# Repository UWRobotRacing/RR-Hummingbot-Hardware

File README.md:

# RobotRacing2019-Hardware
This repo contains hardware includes mech &amp; electrical. Firmware code will also locate here.

## Code Style
1. Use `space: 2` for tabs
2. Preferrably to put all private global variables within a local struct called `FileName_data_S`, and declare a static global variable `FileName_data_S fileName_data;` & initialized with a `memset(&fileName_data, 0, sizeof(fileName_data));` 
    - Reason: to keep global vars more organized and trackable
3. use **cameralCase** preferrably for the variable names and function names
4. For libraries, we shall append a unique space name in CAP before each public functions such as `uint8_t RF24_read(void)`
5. All private data & functions should be declared with a `static`, so it clearly indicate the function/data is private.

## Key Notes
1. For Mac users to use uart for debugging, you will be required to install [FT232R driver](https://www.ftdichip.com/Drivers/VCP.htm), please see instructions here: - [MacOS High Sierra 10.13.3 FTDI Driver Fix](https://superuser.com/questions/1135730/how-to-release-reset-serial-port-ftdi-devices-mac-osx)
2. NXP mcuxpresso API for our chip: [link](https://mcuxpresso.nxp.com/api_doc/dev/1008/group__lpspi__driver.html#ae03069cfdcf680ee5fd81e077b81bc18), and you might be required to login, please register an account if necessary.
    - you can also download the API, which contains chip specific examples \[SDK_2.5.0_MKE14F512xxx16\]
3. Our M4 chip: MKE14F512xxx16
  
## Hardware Resources
### Reedy Sonic 540 Sensor 6Pins

IMHO the connector is "EFRA standard" (RC cars)
see here page 25
[http://mgm-compro.com/manuals/en-man...-071011-a1.pdf](http://mgm-compro.com/manuals/en-manual-x-series-071011-a1.pdf)
 - Pin #1 – black wire, ground potential (minus)
 - Pin #2 – orange wire, sensor phase C
 - Pin #3 – white wire, sensor phase B
 - Pin #4 – green wire, sensor phase A
 - Pin #5 – blue wire, motor temperature sensing, 10 k NTC
 - (other end of sensor is on ground potential, pin #1)
 - Pin #6 – red wire, sensors feeding, +5.0 V ± 10%.
(supply voltage for sensors provide controller, don´t connect external voltage !)

#### interfacing hall sensors:
https://tutorial.cytron.io/2018/07/04/measuring-dc-motor-rpm-through-built-in-hall-sensor-encoder/
https://www.nxp.com/docs/en/application-note/AN2892.pdf

### Steering_Encoder:
https://www.digikey.ca/product-detail/en/cui-inc/AMT203-V/102-2050-ND/2278846

### ESC Arduino
https://www.instructables.com/id/ESC-Programming-on-Arduino-Hobbyking-ESC/ 
1000us - 2000us

If a 0-180° servo is designed to respond to 1000-2000 µs pulses, it interprets 1000 µs as “0°” and 2000 µs as “180°.” But, with default pulse width limits range of 544-2400 µs, the Arduino will send a signal of ~1000 µs for an angle of 44°. Sweeping from 1000 to 2000 µs would then only translate to a ~90° swing of the servo arm instead of a full 180°. This, and other potential issues can be avoided if microseconds are used instead of angles in degrees, or if the optional pulse width floor and ceiling parameters are defined in pin setup for each servo.
```c
#define Servo_VERSION           2     // software version of this library
#define MIN_PULSE_WIDTH       544     // the shortest pulse sent to a servo  
#define MAX_PULSE_WIDTH      2400     // the longest pulse sent to a servo 
#define DEFAULT_PULSE_WIDTH  1500     // default pulse width when servo is attached
#define REFRESH_INTERVAL    20000     // minumim time to refresh servos in microseconds 

```

### nRF24L01
1. [Intro](https://components101.com/wireless/nrf24l01-pinout-features-datasheet)
2. [DataSheet](https://components101.com/sites/default/files/component_datasheet/nRF24L01%20Datasheet.pdf)
3. [Enhancing](https://www.instructables.com/id/Enhanced-NRF24L01/)
4. [Detailed Explaination](http://www.diyembedded.com/tutorials/nrf24l01_0/nrf24l01_tutorial_0.pdf)
5. [Colorful InDepth Descriptions](https://lastminuteengineers.com/nrf24l01-arduino-wireless-communication/)

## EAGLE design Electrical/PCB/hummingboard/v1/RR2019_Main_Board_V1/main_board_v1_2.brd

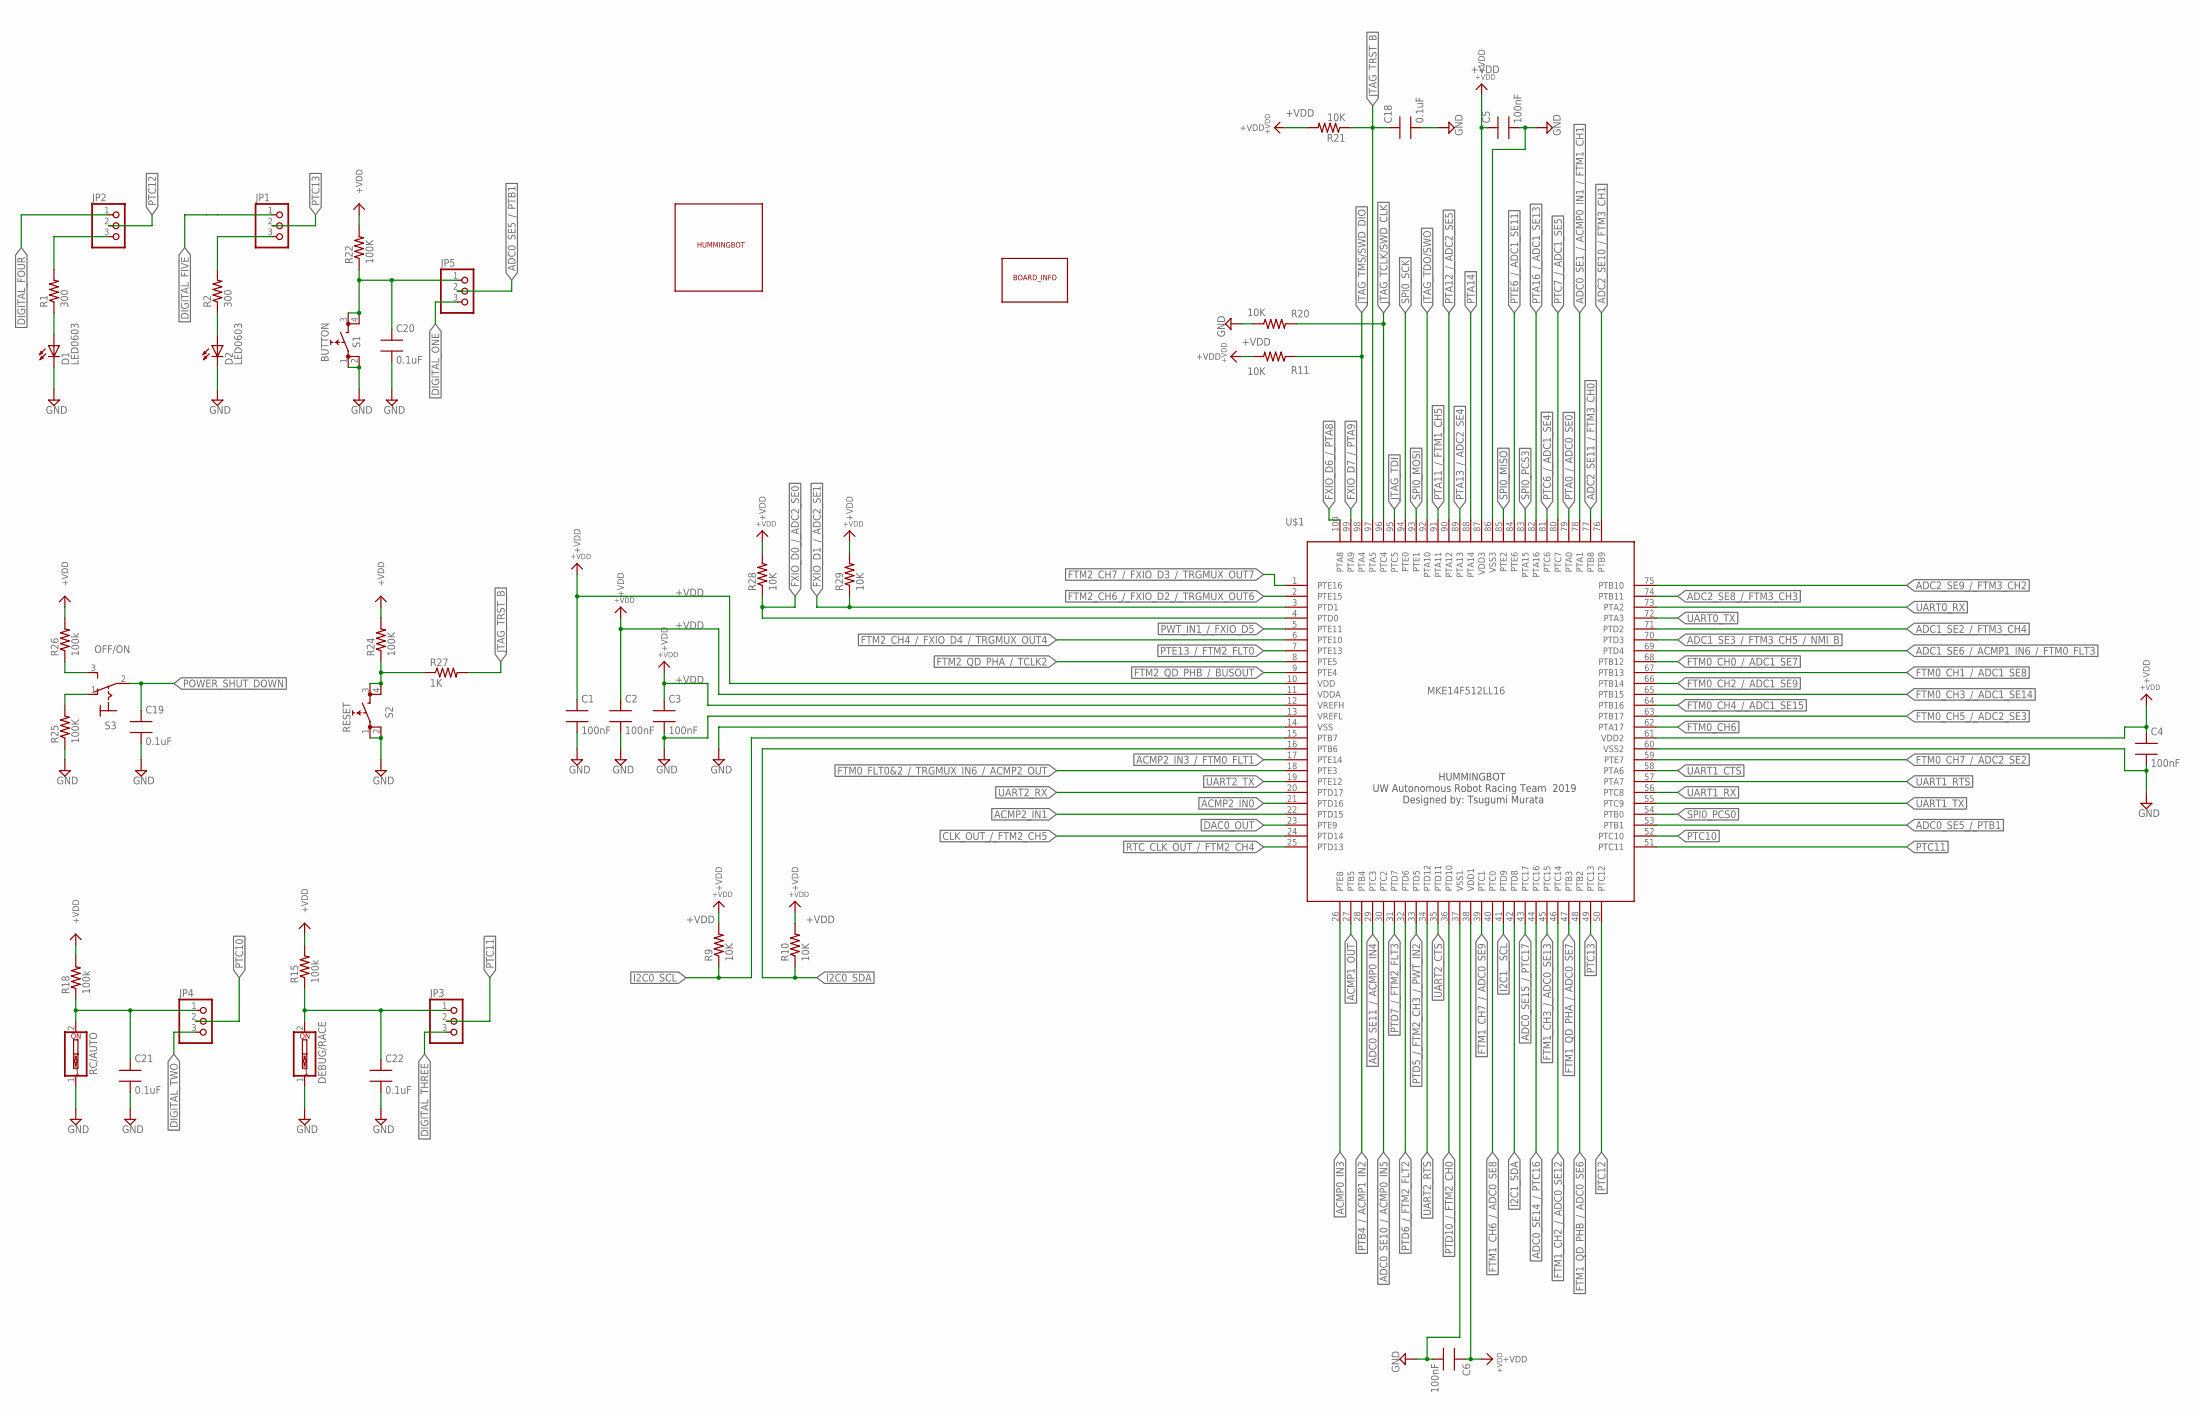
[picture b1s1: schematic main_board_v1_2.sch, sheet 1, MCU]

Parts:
C1, C2, C3, C4, C5, C6: 100nF; 0603SMT
C18, C19, C20, C21, C22: 0.1uF; 0603SMT
D1, D2: LED0603; 0603SMT
DEBUG/RACE: SW_DIP-1; EDG-01
JP1, JP2, JP3, JP4, JP5: PINHD-1X3; 1X03
R1, R2: 300; 0603SMT
R9, R10, R11, R20, R21, R28, R29: 10K; 0603SMT
R15, R18, R26: 100k; 0603SMT
R22, R24, R25: 100K; 0603SMT
R27: 1K; 0603SMT
RC/AUTO: SW_DIP-1; EDG-01
S1: BUTTON; TACT_SWITCH_SMT
S2: RESET; TACT_SWITCH_SMT
S3: OFF/ON; M9040P
U$1: MKE14F512LL16; LQFP100
U$38: BOARD_INFO
U$44: TEAM_LOGO

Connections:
+VDD: C1.1, C2.1, C3.1, C4.1, C5.1, C6.1, R9.2, R10.2, R11.2, R15.2, R18.2, R21.2, R22.2, R24.2, R26.2, R28.2, R29.2, U$1.10 (VDD), U$1.11 (VDDA), U$1.12 (VREFH), U$1.38 (VDD1), U$1.61 (VDD2), U$1.87 (VDD3); also elsewhere on the board
ACMP0_IN3: U$1.26 (PTE8); also elsewhere on the board
ACMP1_OUT: U$1.27 (PTB5); also elsewhere on the board
ACMP2_IN0: U$1.21 (PTD16); also elsewhere on the board
ACMP2_IN1: U$1.22 (PTD15); also elsewhere on the board
ACMP2_IN3_/_FTM0_FLT1: U$1.17 (PTE14); also elsewhere on the board
ADC0_SE1_/_ACMP0_IN1_/_FTM1_CH1: U$1.78 (PTA1); also elsewhere on the board
ADC0_SE5_/_PTB1: JP5.2, U$1.53 (PTB1)
ADC0_SE10_/_ACMP0_IN5: U$1.30 (PTC2); also elsewhere on the board
ADC0_SE11_/_ACMP0_IN4: U$1.29 (PTC3); also elsewhere on the board
ADC0_SE14_/_PTC16: U$1.44 (PTC16); also elsewhere on the board
ADC0_SE15_/_PTC17: U$1.43 (PTC17); also elsewhere on the board
ADC1_SE2_/_FTM3_CH4: U$1.71 (PTD2); also elsewhere on the board
ADC1_SE3_/_FTM3_CH5_/_NMI_B: U$1.70 (PTD3); also elsewhere on the board
ADC1_SE6_/_ACMP1_IN6_/_FTM0_FLT3: U$1.69 (PTD4); also elsewhere on the board
ADC2_SE8_/_FTM3_CH3: U$1.74 (PTB11); also elsewhere on the board
ADC2_SE9_/_FTM3_CH2: U$1.75 (PTB10); also elsewhere on the board
ADC2_SE10_/_FTM3_CH1: U$1.76 (PTB9); also elsewhere on the board
ADC2_SE11_/_FTM3_CH0: U$1.77 (PTB8); also elsewhere on the board
CLK_OUT_/_FTM2_CH5: U$1.24 (PTD14); also elsewhere on the board
DAC0_OUT: U$1.23 (PTE9); also elsewhere on the board
DIGITAL_FIVE: JP1.1; also elsewhere on the board
DIGITAL_FOUR: JP2.1; also elsewhere on the board
DIGITAL_ONE: JP5.3; also elsewhere on the board
DIGITAL_THREE: JP3.3; also elsewhere on the board
DIGITAL_TWO: JP4.3; also elsewhere on the board
FTM0_CH0_/_ADC1_SE7: U$1.68 (PTB12); also elsewhere on the board
FTM0_CH1_/_ADC1_SE8: U$1.67 (PTB13); also elsewhere on the board
FTM0_CH2_/_ADC1_SE9: U$1.66 (PTB14); also elsewhere on the board
FTM0_CH3_/_ADC1_SE14: U$1.65 (PTB15); also elsewhere on the board
FTM0_CH4_/_ADC1_SE15: U$1.64 (PTB16); also elsewhere on the board
FTM0_CH5_/_ADC2_SE3: U$1.63 (PTB17); also elsewhere on the board
FTM0_CH6: U$1.62 (PTA17); also elsewhere on the board
FTM0_CH7_/_ADC2_SE2: U$1.59 (PTE7); also elsewhere on the board
FTM0_FLT0&2_/_TRGMUX_IN6_/_ACMP2_OUT: U$1.18 (PTE3); also elsewhere on the board
FTM1_CH2_/_ADC0_SE12: U$1.46 (PTC14); also elsewhere on the board
FTM1_CH3_/_ADC0_SE13: U$1.45 (PTC15); also elsewhere on the board
FTM1_CH6_/_ADC0_SE8: U$1.40 (PTC0); also elsewhere on the board
FTM1_CH7_/_ADC0_SE9: U$1.39 (PTC1); also elsewhere on the board
FTM1_QD_PHA_/_ADC0_SE7: U$1.47 (PTB3); also elsewhere on the board
FTM1_QD_PHB_/_ADC0_SE6: U$1.48 (PTB2); also elsewhere on the board
FTM2_CH4_/_FXIO_D4_/_TRGMUX_OUT4: U$1.6 (PTE10); also elsewhere on the board
FTM2_CH6_/_FXIO_D2_/_TRGMUX_OUT6: U$1.2 (PTE15); also elsewhere on the board
FTM2_CH7_/_FXIO_D3_/_TRGMUX_OUT7: U$1.1 (PTE16); also elsewhere on the board
FTM2_QD_PHA_/_TCLK2: U$1.8 (PTE5); also elsewhere on the board
FTM2_QD_PHB_/_BUSOUT: U$1.9 (PTE4); also elsewhere on the board
FXIO_D0_/_ADC2_SE0: R28.1, U$1.4 (PTD0); also elsewhere on the board
FXIO_D1_/_ADC2_SE1: R29.1, U$1.3 (PTD1); also elsewhere on the board
FXIO_D6_/_PTA8: U$1.100 (PTA8); also elsewhere on the board
FXIO_D7_/_PTA9: U$1.99 (PTA9); also elsewhere on the board
GND: C1.2, C2.2, C3.2, C4.2, C5.2, C6.2, C18.2, C19.2, C20.2, C21.2, C22.2, D1.2 (C), D2.2 (C), DEBUG/RACE.1, R20.1, R25.1, RC/AUTO.1, S1.1 (0), S1.2 (0), S2.1 (0), S2.2 (0), U$1.13 (VREFL), U$1.14 (VSS), U$1.37 (VSS1), U$1.60 (VSS2), U$1.86 (VSS3); also elsewhere on the board
I2C0_SCL: R9.1, U$1.15 (PTB7); also elsewhere on the board
I2C0_SDA: R10.1, U$1.16 (PTB6); also elsewhere on the board
I2C1_SDA: U$1.42 (PTD8); also elsewhere on the board
I2C1__SCL: U$1.41 (PTD9); also elsewhere on the board
JTAG_TCLK/SWD_CLK: R20.2, U$1.96 (PTC4); also elsewhere on the board
JTAG_TDI: U$1.95 (PTC5); also elsewhere on the board
JTAG_TDO/SWO: U$1.92 (PTA10); also elsewhere on the board
JTAG_TMS/SWD_DIO: R11.1, U$1.98 (PTA4); also elsewhere on the board
JTAG_TRST_B: C18.1, R21.1, R27.2, U$1.97 (PTA5); also elsewhere on the board
unnamed: D1.1 (A), R1.1
unnamed: D2.1 (A), R2.1
unnamed: JP1.3, R2.2
unnamed: JP2.3, R1.2
unnamed: R24.1, R27.1, S2.3 (1), S2.4 (1)
unnamed: C22.1, DEBUG/RACE.2, JP3.1, R15.1
unnamed: C21.1, JP4.1, R18.1, RC/AUTO.2
unnamed: C20.1, JP5.1, R22.1, S1.3 (1), S1.4 (1)
unnamed: R26.1, S3.3 (S)
unnamed: R25.2, S3.1 (O)
POWER_SHUT_DOWN: C19.1, S3.2; also elsewhere on the board
PTA0_/_ADC0_SE0: U$1.79 (PTA0); also elsewhere on the board
PTA11_/_FTM1_CH5: U$1.91 (PTA11); also elsewhere on the board
PTA12_/_ADC2_SE5: U$1.90 (PTA12); also elsewhere on the board
PTA13_/_ADC2_SE4: U$1.89 (PTA13); also elsewhere on the board
PTA14: U$1.88 (PTA14); also elsewhere on the board
PTA16_/_ADC1_SE13: U$1.82 (PTA16); also elsewhere on the board
PTB4_/_ACMP1_IN2: U$1.28 (PTB4); also elsewhere on the board
PTC6_/_ADC1_SE4: U$1.81 (PTC6); also elsewhere on the board
PTC7_/_ADC1_SE5: U$1.80 (PTC7); also elsewhere on the board
PTC10: JP4.2, U$1.52 (PTC10)
PTC11: JP3.2, U$1.51 (PTC11)
PTC12: JP2.2, U$1.50 (PTC12)
PTC13: JP1.2, U$1.49 (PTC13)
PTD5_/_FTM2_CH3_/_PWT_IN2: U$1.33 (PTD5); also elsewhere on the board
PTD6_/_FTM2_FLT2: U$1.32 (PTD6); also elsewhere on the board
PTD7_/_FTM2_FLT3: U$1.31 (PTD7); also elsewhere on the board
PTD10_/_FTM2_CH0: U$1.36 (PTD10); also elsewhere on the board
PTE6_/_ADC1_SE11: U$1.84 (PTE6); also elsewhere on the board
PTE13_/_FTM2_FLT0: U$1.7 (PTE13); also elsewhere on the board
PWT_IN1_/_FXIO_D5: U$1.5 (PTE11); also elsewhere on the board
RTC_CLK_OUT_/_FTM2_CH4: U$1.25 (PTD13); also elsewhere on the board
SPI0_MISO: U$1.93 (PTE1); also elsewhere on the board
SPI0_MOSI: U$1.85 (PTE2); also elsewhere on the board
SPI0_PCS0: U$1.54 (PTB0); also elsewhere on the board
SPI0_PCS3: U$1.83 (PTA15); also elsewhere on the board
SPI0_SCK: U$1.94 (PTE0); also elsewhere on the board
UART0_RX: U$1.73 (PTA2); also elsewhere on the board
UART0_TX: U$1.72 (PTA3); also elsewhere on the board
UART1_CTS: U$1.58 (PTA6); also elsewhere on the board
UART1_RTS: U$1.57 (PTA7); also elsewhere on the board
UART1_RX: U$1.56 (PTC8); also elsewhere on the board
UART1_TX: U$1.55 (PTC9); also elsewhere on the board
UART2_CTS: U$1.35 (PTD11); also elsewhere on the board
UART2_RTS: U$1.34 (PTD12); also elsewhere on the board
UART2_RX: U$1.20 (PTD17); also elsewhere on the board
UART2_TX: U$1.19 (PTE12); also elsewhere on the board

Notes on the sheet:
HUMMINGBOT UW Autonomous Robot Racing Team 2019 Designed by: Tsugumi Murata

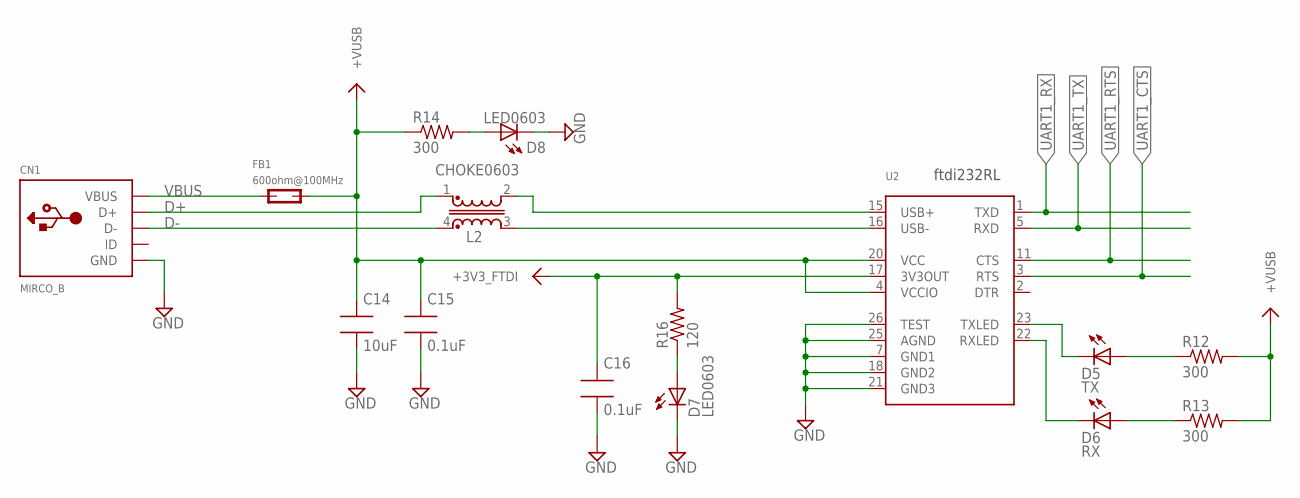
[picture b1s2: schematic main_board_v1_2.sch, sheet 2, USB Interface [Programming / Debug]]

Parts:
C14: 10uF; 0603SMT
C15, C16: 0.1uF; 0603SMT
CN1: MIRCO_B; MICRO-USB
D5: TX; 0603SMT
D6: RX; 0603SMT
D7, D8: LED0603; 0603SMT
FB1: 600ohm@100MHz; 0603SMT
L2: CHOKE0603
R12, R13, R14: 300; 0603SMT
R16: 120; 0603SMT
U2: FT232RLSSOP28; SSOP28DB

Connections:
+3V3_FTDI: C16.1, R16.2, U2.17 (3V3OUT)
+VUSB: C14.1, C15.1, FB1.2, R12.2, R13.2, R14.1, U2.4 (VCCIO), U2.20 (VCC)
D+: CN1.3 (D+), L2.1
D-: CN1.2 (D-), L2.4
GND: C14.2, C15.2, C16.2, CN1.5 (GND), CN1.GND1 (GND), CN1.GND2 (GND), D7.2 (C), D8.2 (C), U2.7 (GND1), U2.18 (GND2), U2.21 (GND3), U2.25 (AGND), U2.26 (TEST); also elsewhere on the board
unnamed: D7.1 (A), R16.1
unnamed: D8.1 (A), R14.2
unnamed: L2.2, U2.15 (USB+)
unnamed: L2.3, U2.16 (USB-)
unnamed: D5.2 (C), U2.23 (TXLED)
unnamed: D5.1 (A), R12.1
unnamed: D6.2 (C), U2.22 (RXLED)
unnamed: D6.1 (A), R13.1
UART1_CTS: U2.3 (RTS); also elsewhere on the board
UART1_RTS: U2.11 (CTS); also elsewhere on the board
UART1_RX: U2.1 (TXD); also elsewhere on the board
UART1_TX: U2.5 (RXD); also elsewhere on the board
VBUS: CN1.1 (VBUS), FB1.1

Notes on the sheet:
ftdi232RL

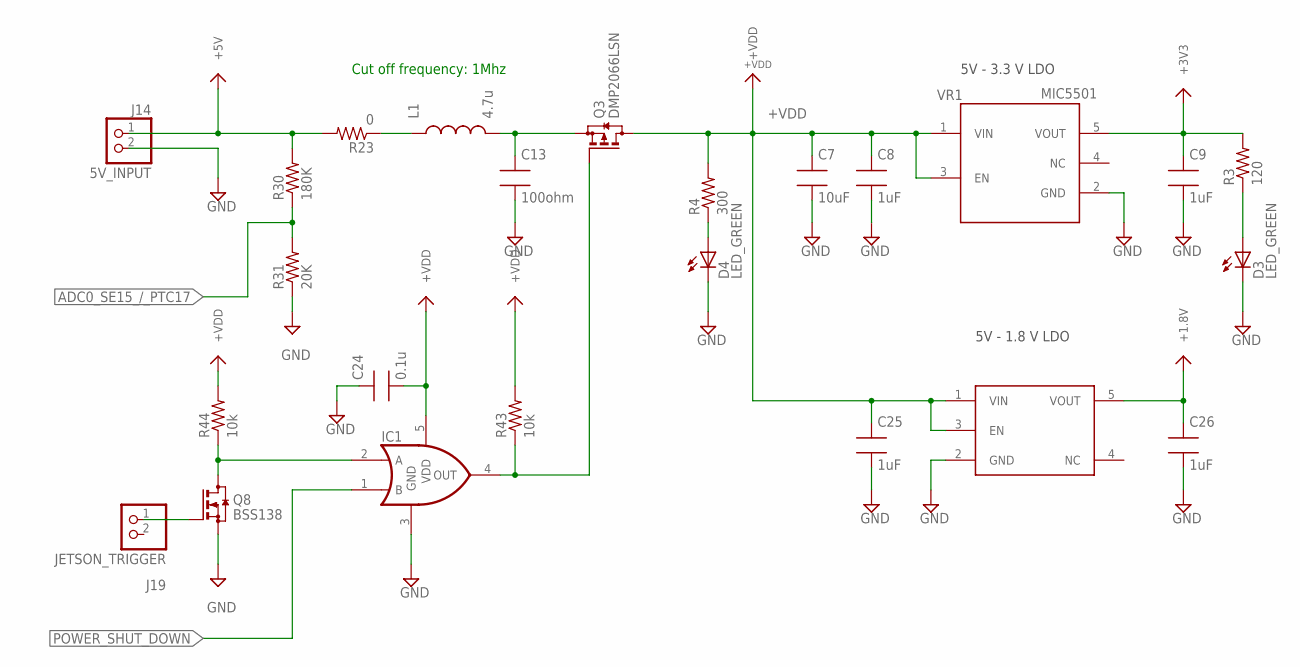
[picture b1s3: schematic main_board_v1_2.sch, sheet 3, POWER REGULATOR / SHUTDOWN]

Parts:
C7: 10uF; 0603SMT
C8, C9, C25, C26: 1uF; 0603SMT
C13: 100ohm; 0603SMT
C24: 0.1u; 0603SMT
D3, D4: LED_GREEN; 0603SMT
IC1: OR_SC70-5; SC70-5
J14: 5V_INPUT; JST_B2B-PH-K-S(LF)(SN)
J19: JETSON_TRIGGER; JST_B2B-PH-K-S(LF)(SN)
L1: 4.7u; 0603SMT
Q3: DMP2066LSN; SOT23
Q8: BSS138; SOT23
R3: 120; 0603SMT
R4: 300; 0603SMT
R23: 0; 0603SMT
R30: 180K; 0603SMT
R31: 20K; 0603SMT
R43, R44: 10k; 0603SMT
VR1: MIC5501; SOT23-5
VR2: ADP121-AUJZ18; TSOT23-5

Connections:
+1.8V: C26.1, VR2.5 (VOUT); also elsewhere on the board
+3V3: C9.1, R3.2, VR1.5 (VOUT); also elsewhere on the board
+5V: J14.1, R23.2, R30.2; also elsewhere on the board
+VDD: C7.1, C8.1, C24.2, C25.1, IC1.5 (VDD), Q3.3 (D), R4.2, R43.2, R44.2, VR1.1 (VIN), VR1.3 (EN), VR2.1 (VIN), VR2.3 (EN); also elsewhere on the board
ADC0_SE15_/_PTC17: R30.1, R31.2; also elsewhere on the board
GND: C7.2, C8.2, C9.2, C13.2, C24.1, C25.2, C26.2, D3.2 (C), D4.2 (C), IC1.3 (GND), J14.2, Q8.2 (S), R31.1, VR1.2 (GND), VR2.2 (GND); also elsewhere on the board
unnamed: D3.1 (A), R3.1
unnamed: D4.1 (A), R4.1
unnamed: L1.1, R23.1
unnamed: C13.1, L1.2, Q3.2 (S)
unnamed: J19.1, Q8.1 (G)
unnamed: IC1.2 (A), Q8.3 (D), R44.1
unnamed: IC1.4 (OUT), Q3.1 (G), R43.1
POWER_SHUT_DOWN: IC1.1 (B); also elsewhere on the board

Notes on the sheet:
5V - 3.3 V LDO
5V - 1.8 V LDO
Cut off frequency: 1Mhz

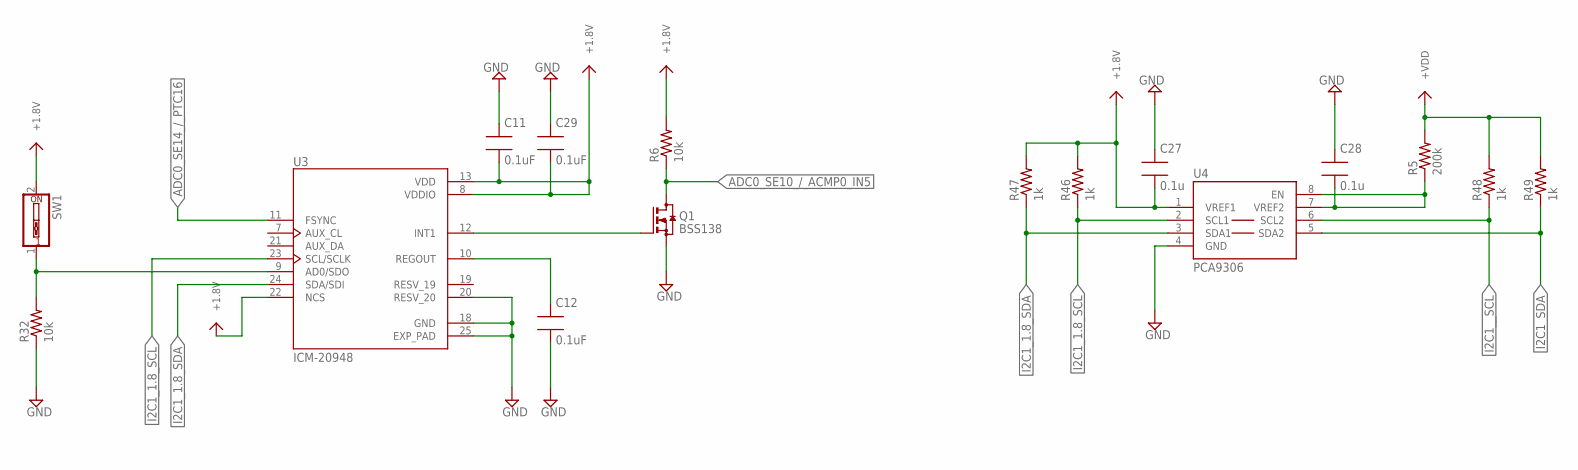
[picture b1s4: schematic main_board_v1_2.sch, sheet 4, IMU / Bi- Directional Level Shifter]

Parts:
C11, C12, C29: 0.1uF; 0603SMT
C27, C28: 0.1u; 0603SMT
Q1: BSS138; SOT23
R5: 200k; 0603SMT
R6, R32: 10k; 0603SMT
R46, R47, R48, R49: 1k; 0603SMT
SW1: SW_DIP-1; EDG-01
U3: ICM-20948; QFN40P300X300X105-25N
U4: PCA9306; PSOP-8

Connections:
+1.8V: C11.2, C27.2, C29.2, R6.2, R46.2, R47.2, SW1.2, U3.8 (VDDIO), U3.13 (VDD), U3.22 (NCS), U4.1 (VREF1); also elsewhere on the board
+VDD: R5.2, R48.2, R49.2; also elsewhere on the board
ADC0_SE10_/_ACMP0_IN5: Q1.3 (D), R6.1; also elsewhere on the board
ADC0_SE14_/_PTC16: U3.11 (FSYNC); also elsewhere on the board
GND: C11.1, C12.2, C27.1, C28.1, C29.1, Q1.2 (S), R32.1, U3.18 (GND), U3.20 (RESV_20), U3.25 (EXP_PAD), U4.4 (GND); also elsewhere on the board
I2C1_1.8_SCL: R46.1, U3.23 (SCL/SCLK), U4.2 (SCL1); also elsewhere on the board
I2C1_1.8_SDA: R47.1, U3.24 (SDA/SDI), U4.3 (SDA1); also elsewhere on the board
I2C1_SDA: R49.1, U4.5 (SDA2); also elsewhere on the board
I2C1__SCL: R48.1, U4.6 (SCL2); also elsewhere on the board
unnamed: C12.1, U3.10 (REGOUT)
unnamed: C28.2, R5.1, U4.7 (VREF2), U4.8 (EN)
unnamed: R32.2, SW1.1, U3.9 (AD0/SDO)
unnamed: Q1.1 (G), U3.12 (INT1)

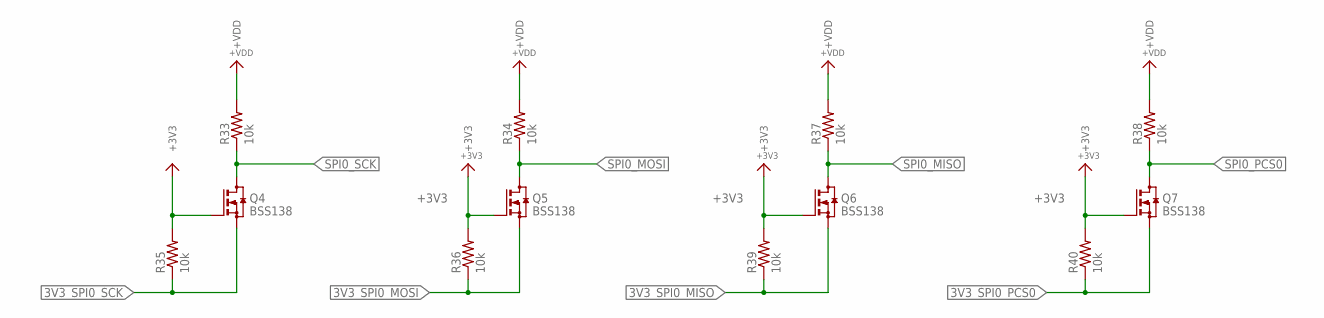
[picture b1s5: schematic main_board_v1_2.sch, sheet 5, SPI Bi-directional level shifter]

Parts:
Q4, Q5, Q6, Q7: BSS138; SOT23
R33, R34, R35, R36, R37, R38, R39, R40: 10k; 0603SMT

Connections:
3V3_SPI0_MISO: Q5.2 (S), R36.1; also elsewhere on the board
3V3_SPI0_MOSI: Q6.2 (S), R39.1; also elsewhere on the board
3V3_SPI0_PCS0: Q7.2 (S), R40.1; also elsewhere on the board
3V3_SPI0_SCK: Q4.2 (S), R35.1; also elsewhere on the board
+3V3: Q4.1 (G), Q5.1 (G), Q6.1 (G), Q7.1 (G), R35.2, R36.2, R39.2, R40.2; also elsewhere on the board
+VDD: R33.2, R34.2, R37.2, R38.2; also elsewhere on the board
SPI0_MISO: Q5.3 (D), R34.1; also elsewhere on the board
SPI0_MOSI: Q6.3 (D), R37.1; also elsewhere on the board
SPI0_PCS0: Q7.3 (D), R38.1; also elsewhere on the board
SPI0_SCK: Q4.3 (D), R33.1; also elsewhere on the board

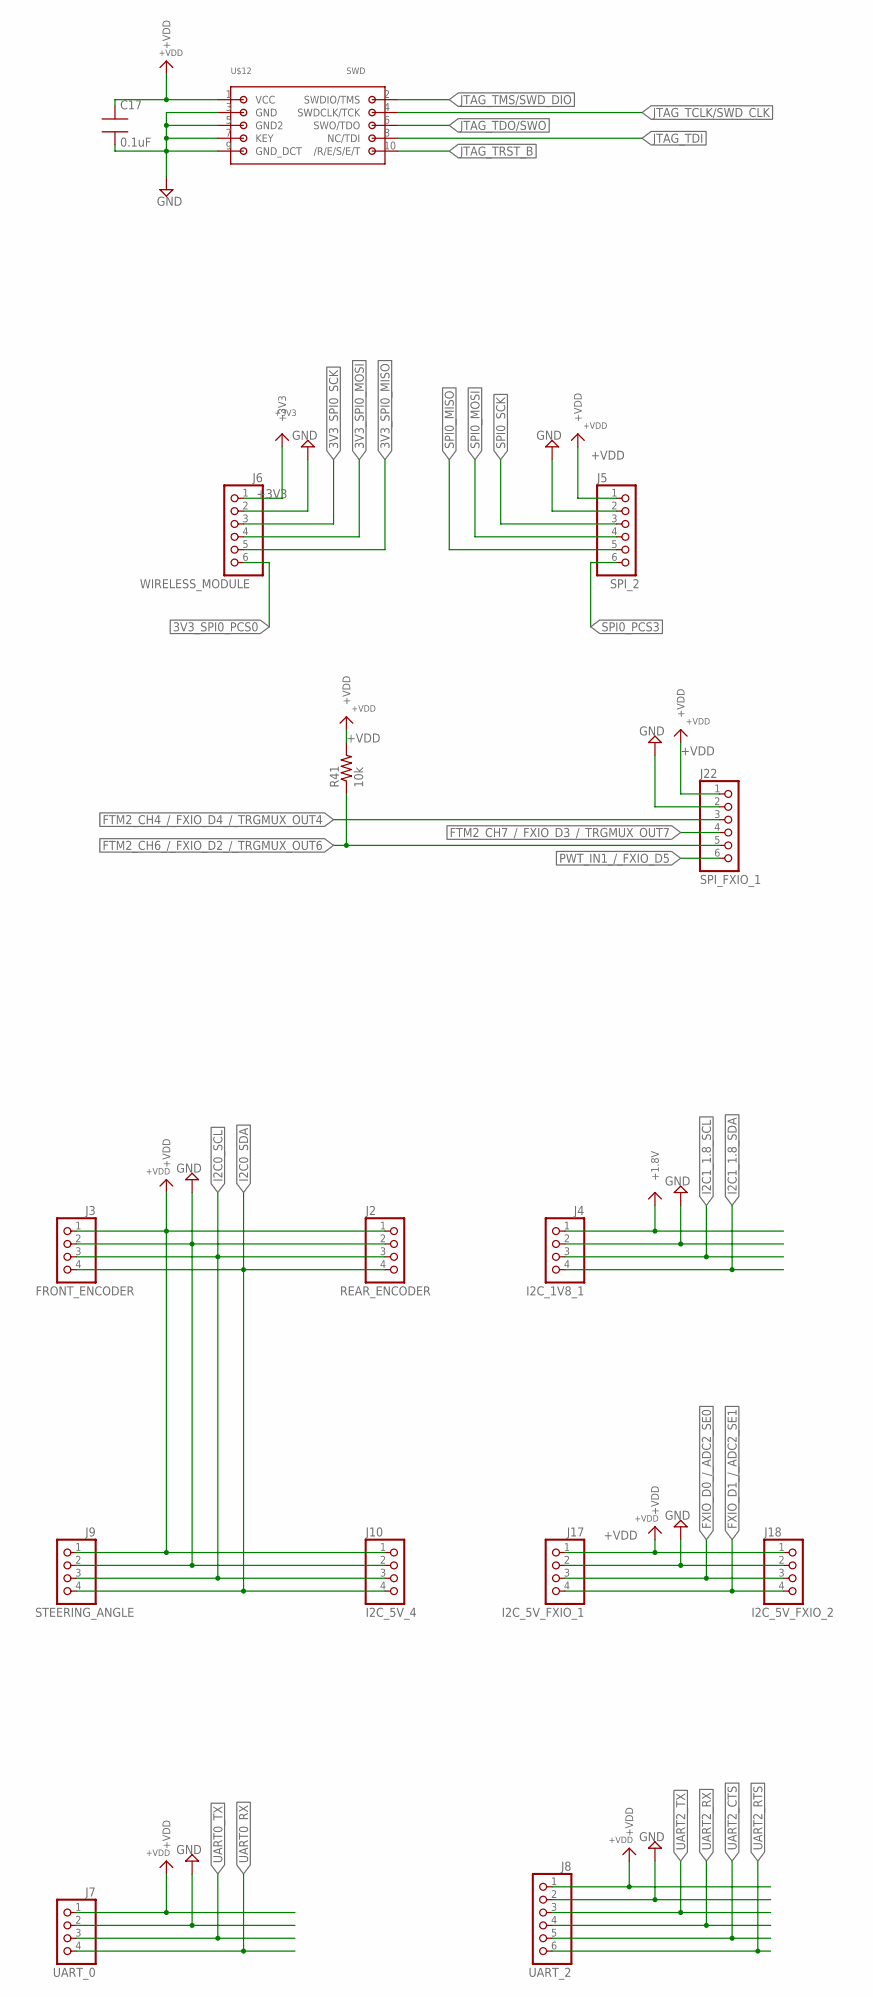
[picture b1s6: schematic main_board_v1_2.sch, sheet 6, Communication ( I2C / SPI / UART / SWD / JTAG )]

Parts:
C17: 0.1uF; 0603SMT
J2: REAR_ENCODER; JST_B4B-PH-K-S(LF)(SN)
J3: FRONT_ENCODER; JST_B4B-PH-K-S(LF)(SN)
J4: I2C_1V8_1; JST_B4B-PH-K-S(LF)(SN)
J5: SPI_2; JST_B6B-PH-K-S(LF)(SN)
J6: WIRELESS_MODULE; JST_B6B-PH-K-S(LF)(SN)
J7: UART_0; JST_B4B-PH-K-S(LF)(SN)
J8: UART_2; JST_B6B-PH-K-S(LF)(SN)
J9: STEERING_ANGLE; JST_B4B-PH-K-S(LF)(SN)
J10: I2C_5V_4; JST_B4B-PH-K-S(LF)(SN)
J17: I2C_5V_FXIO_1; JST_B4B-PH-K-S(LF)(SN)
J18: I2C_5V_FXIO_2; JST_B4B-PH-K-S(LF)(SN)
J22: SPI_FXIO_1; JST_B6B-PH-K-S(LF)(SN)
R41: 10k; 0603SMT
U$12: SWD; SWD_1.27MM

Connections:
3V3_SPI0_MISO: J6.4; also elsewhere on the board
3V3_SPI0_MOSI: J6.5; also elsewhere on the board
3V3_SPI0_PCS0: J6.6; also elsewhere on the board
3V3_SPI0_SCK: J6.3; also elsewhere on the board
+1.8V: J4.1; also elsewhere on the board
+3V3: J6.1; also elsewhere on the board
+VDD: C17.1, J2.1, J3.1, J5.1, J7.1, J8.1, J9.1, J10.1, J17.1, J18.1, J22.1, R41.2, U$12.1 (VCC); also elsewhere on the board
FTM2_CH4_/_FXIO_D4_/_TRGMUX_OUT4: J22.3; also elsewhere on the board
FTM2_CH6_/_FXIO_D2_/_TRGMUX_OUT6: J22.5, R41.1; also elsewhere on the board
FTM2_CH7_/_FXIO_D3_/_TRGMUX_OUT7: J22.4; also elsewhere on the board
FXIO_D0_/_ADC2_SE0: J17.3, J18.3; also elsewhere on the board
FXIO_D1_/_ADC2_SE1: J17.4, J18.4; also elsewhere on the board
GND: C17.2, J2.2, J3.2, J4.2, J5.2, J6.2, J7.2, J8.2, J9.2, J10.2, J17.2, J18.2, J22.2, U$12.3 (GND), U$12.5 (GND2), U$12.7 (KEY), U$12.9 (GND_DCT); also elsewhere on the board
I2C0_SCL: J2.3, J3.3, J9.3, J10.3; also elsewhere on the board
I2C0_SDA: J2.4, J3.4, J9.4, J10.4; also elsewhere on the board
I2C1_1.8_SCL: J4.3; also elsewhere on the board
I2C1_1.8_SDA: J4.4; also elsewhere on the board
JTAG_TCLK/SWD_CLK: U$12.4 (SWDCLK/TCK); also elsewhere on the board
JTAG_TDI: U$12.8 (NC/TDI); also elsewhere on the board
JTAG_TDO/SWO: U$12.6 (SWO/TDO); also elsewhere on the board
JTAG_TMS/SWD_DIO: U$12.2 (SWDIO/TMS); also elsewhere on the board
JTAG_TRST_B: U$12.10 (/R/E/S/E/T); also elsewhere on the board
PWT_IN1_/_FXIO_D5: J22.6; also elsewhere on the board
SPI0_MISO: J5.4; also elsewhere on the board
SPI0_MOSI: J5.5; also elsewhere on the board
SPI0_PCS3: J5.6; also elsewhere on the board
SPI0_SCK: J5.3; also elsewhere on the board
UART0_RX: J7.4; also elsewhere on the board
UART0_TX: J7.3; also elsewhere on the board
UART2_CTS: J8.5; also elsewhere on the board
UART2_RTS: J8.6; also elsewhere on the board
UART2_RX: J8.4; also elsewhere on the board
UART2_TX: J8.3; also elsewhere on the board

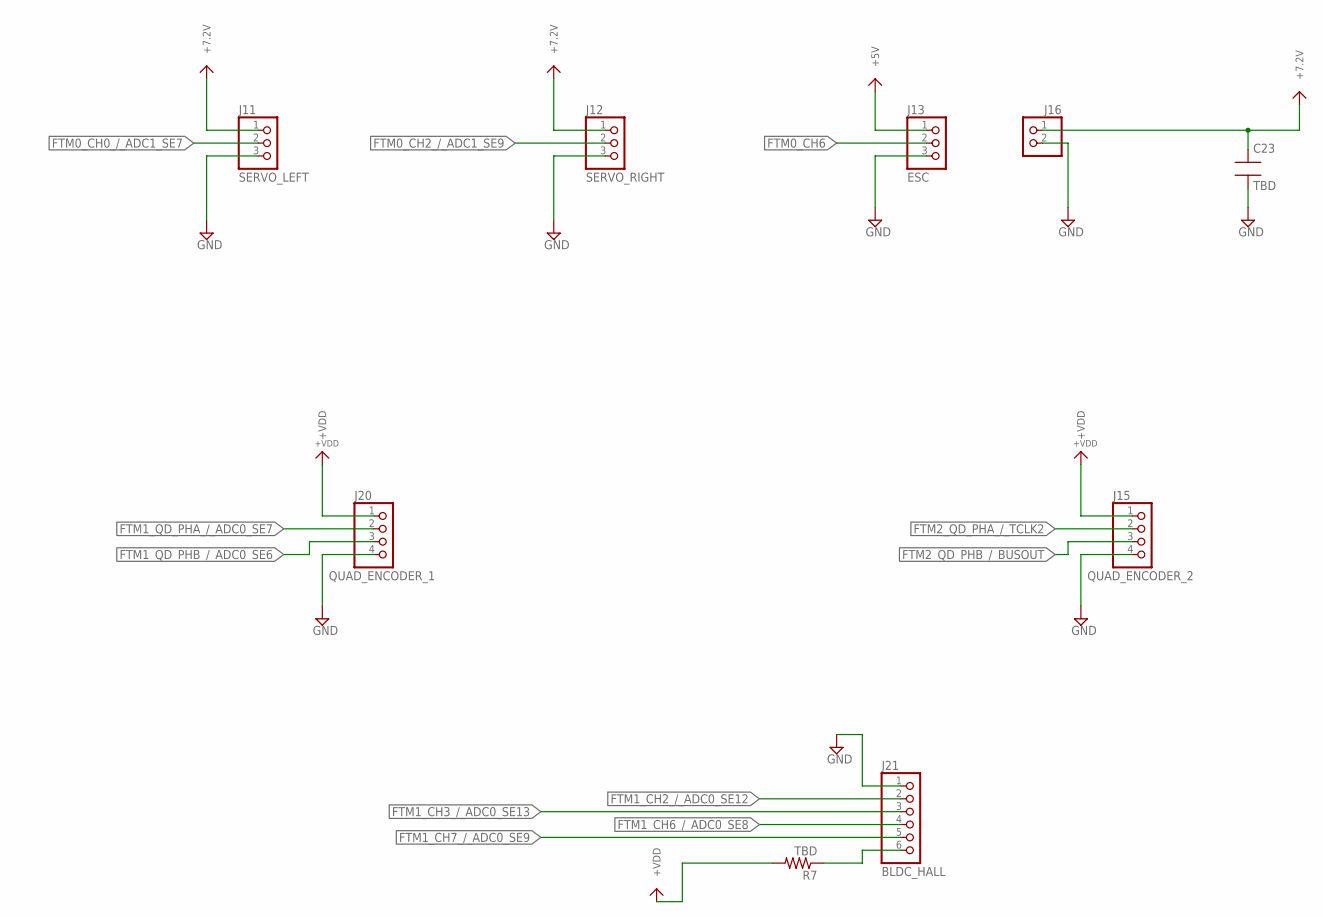
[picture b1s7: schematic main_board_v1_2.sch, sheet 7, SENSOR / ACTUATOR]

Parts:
C23: TBD; 0603SMT
J11: SERVO_LEFT; JST_B3B-PH-K-S(LF)(SN)
J12: SERVO_RIGHT; JST_B3B-PH-K-S(LF)(SN)
J13: ESC; JST_B3B-PH-K-S(LF)(SN)
J15: QUAD_ENCODER_2; JST_B4B-PH-K-S(LF)(SN)
J16: 7.2V_INPUT; JST_B2B-PH-K-S(LF)(SN)
J20: QUAD_ENCODER_1; JST_B4B-PH-K-S(LF)(SN)
J21: BLDC_HALL; JST_B6B-PH-K-S(LF)(SN)
R7: TBD; 0603SMT

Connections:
+5V: J13.1; also elsewhere on the board
+7.2V: C23.1, J11.1, J12.1, J16.1
+VDD: J15.1, J20.1, R7.2; also elsewhere on the board
FTM0_CH0_/_ADC1_SE7: J11.2; also elsewhere on the board
FTM0_CH2_/_ADC1_SE9: J12.2; also elsewhere on the board
FTM0_CH6: J13.2; also elsewhere on the board
FTM1_CH2_/_ADC0_SE12: J21.2; also elsewhere on the board
FTM1_CH3_/_ADC0_SE13: J21.3; also elsewhere on the board
FTM1_CH6_/_ADC0_SE8: J21.4; also elsewhere on the board
FTM1_CH7_/_ADC0_SE9: J21.5; also elsewhere on the board
FTM1_QD_PHA_/_ADC0_SE7: J20.2; also elsewhere on the board
FTM1_QD_PHB_/_ADC0_SE6: J20.3; also elsewhere on the board
FTM2_QD_PHA_/_TCLK2: J15.2; also elsewhere on the board
FTM2_QD_PHB_/_BUSOUT: J15.3; also elsewhere on the board
GND: C23.2, J11.3, J12.3, J13.3, J15.4, J16.2, J20.4, J21.1; also elsewhere on the board
unnamed: J21.6, R7.1

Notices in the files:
parts and their libraries:
microbuilder: This work is placed in the public domain, and may be freely used for commercial and non-commercial work with the following conditions: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
